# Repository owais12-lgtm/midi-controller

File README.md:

# midi-controller
A MIDI keyboard is basically just a controller. You can use it to trigger notes on a synth or plugin, you can assign the encoder to volume, LFO rate or anything else. So if you don't connect it to anything you won't get any sound.

tldr: its a smaller more weirder keyboard that can help you make music!

# features
- 6 rotary knobs for menu/Midi control
- 4 sliders
- 25 macro keys
- rp2040 based micro controller 
- choc switches
# Images

# CAD

https://www.tinkercad.com/things/4G5PN0rRYm5-midi-controller-v2

# BOM
| Name | Purpose | Quantity | Total Cost (USD) | Link | Distributor |
|------|---------|----------|-----------------|------|-------------|
| switch | switch | 30 | $10.00 | [stackskb.com](https://stackskb.com/store/ttc-low-profile-brown-switches-tactile/) | stacks |
| rpi pico | mcu | 1 | $7.00 | [robu](https://www.google.com/search?client=firefox-b-d&q=rpi+pico+robu) | robu |
| pcb | pcb | 1 | $30.00 | [lioncircuits.com](https://www.lioncircuits.com/quote) | lion pcb |

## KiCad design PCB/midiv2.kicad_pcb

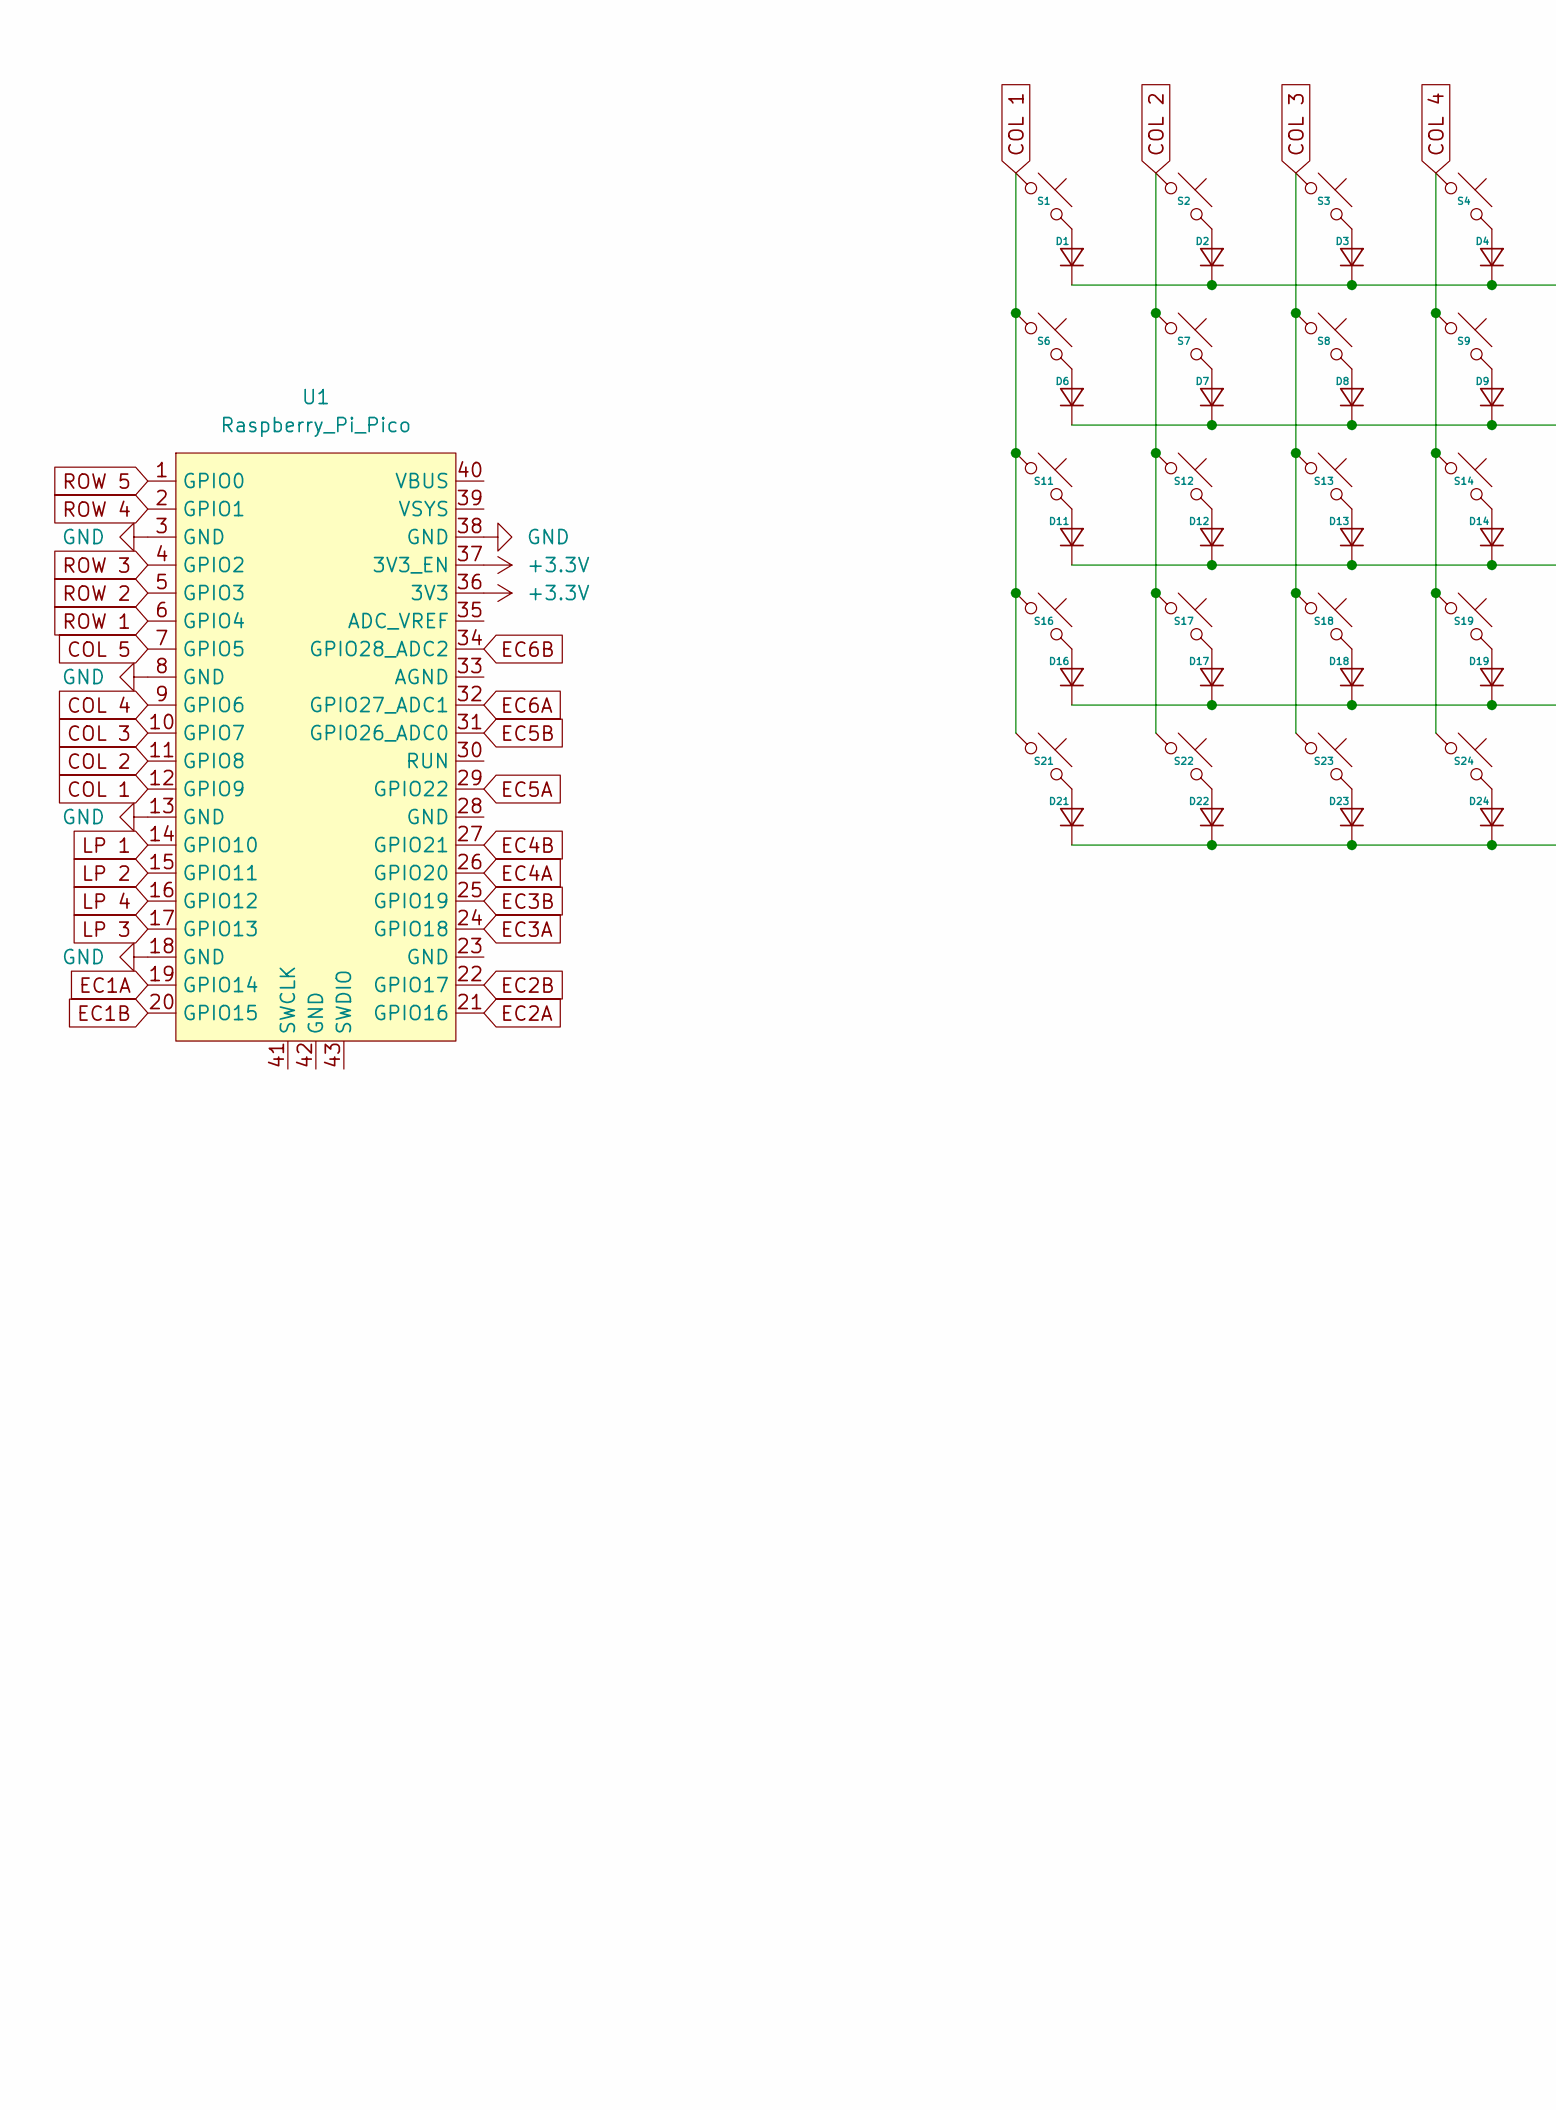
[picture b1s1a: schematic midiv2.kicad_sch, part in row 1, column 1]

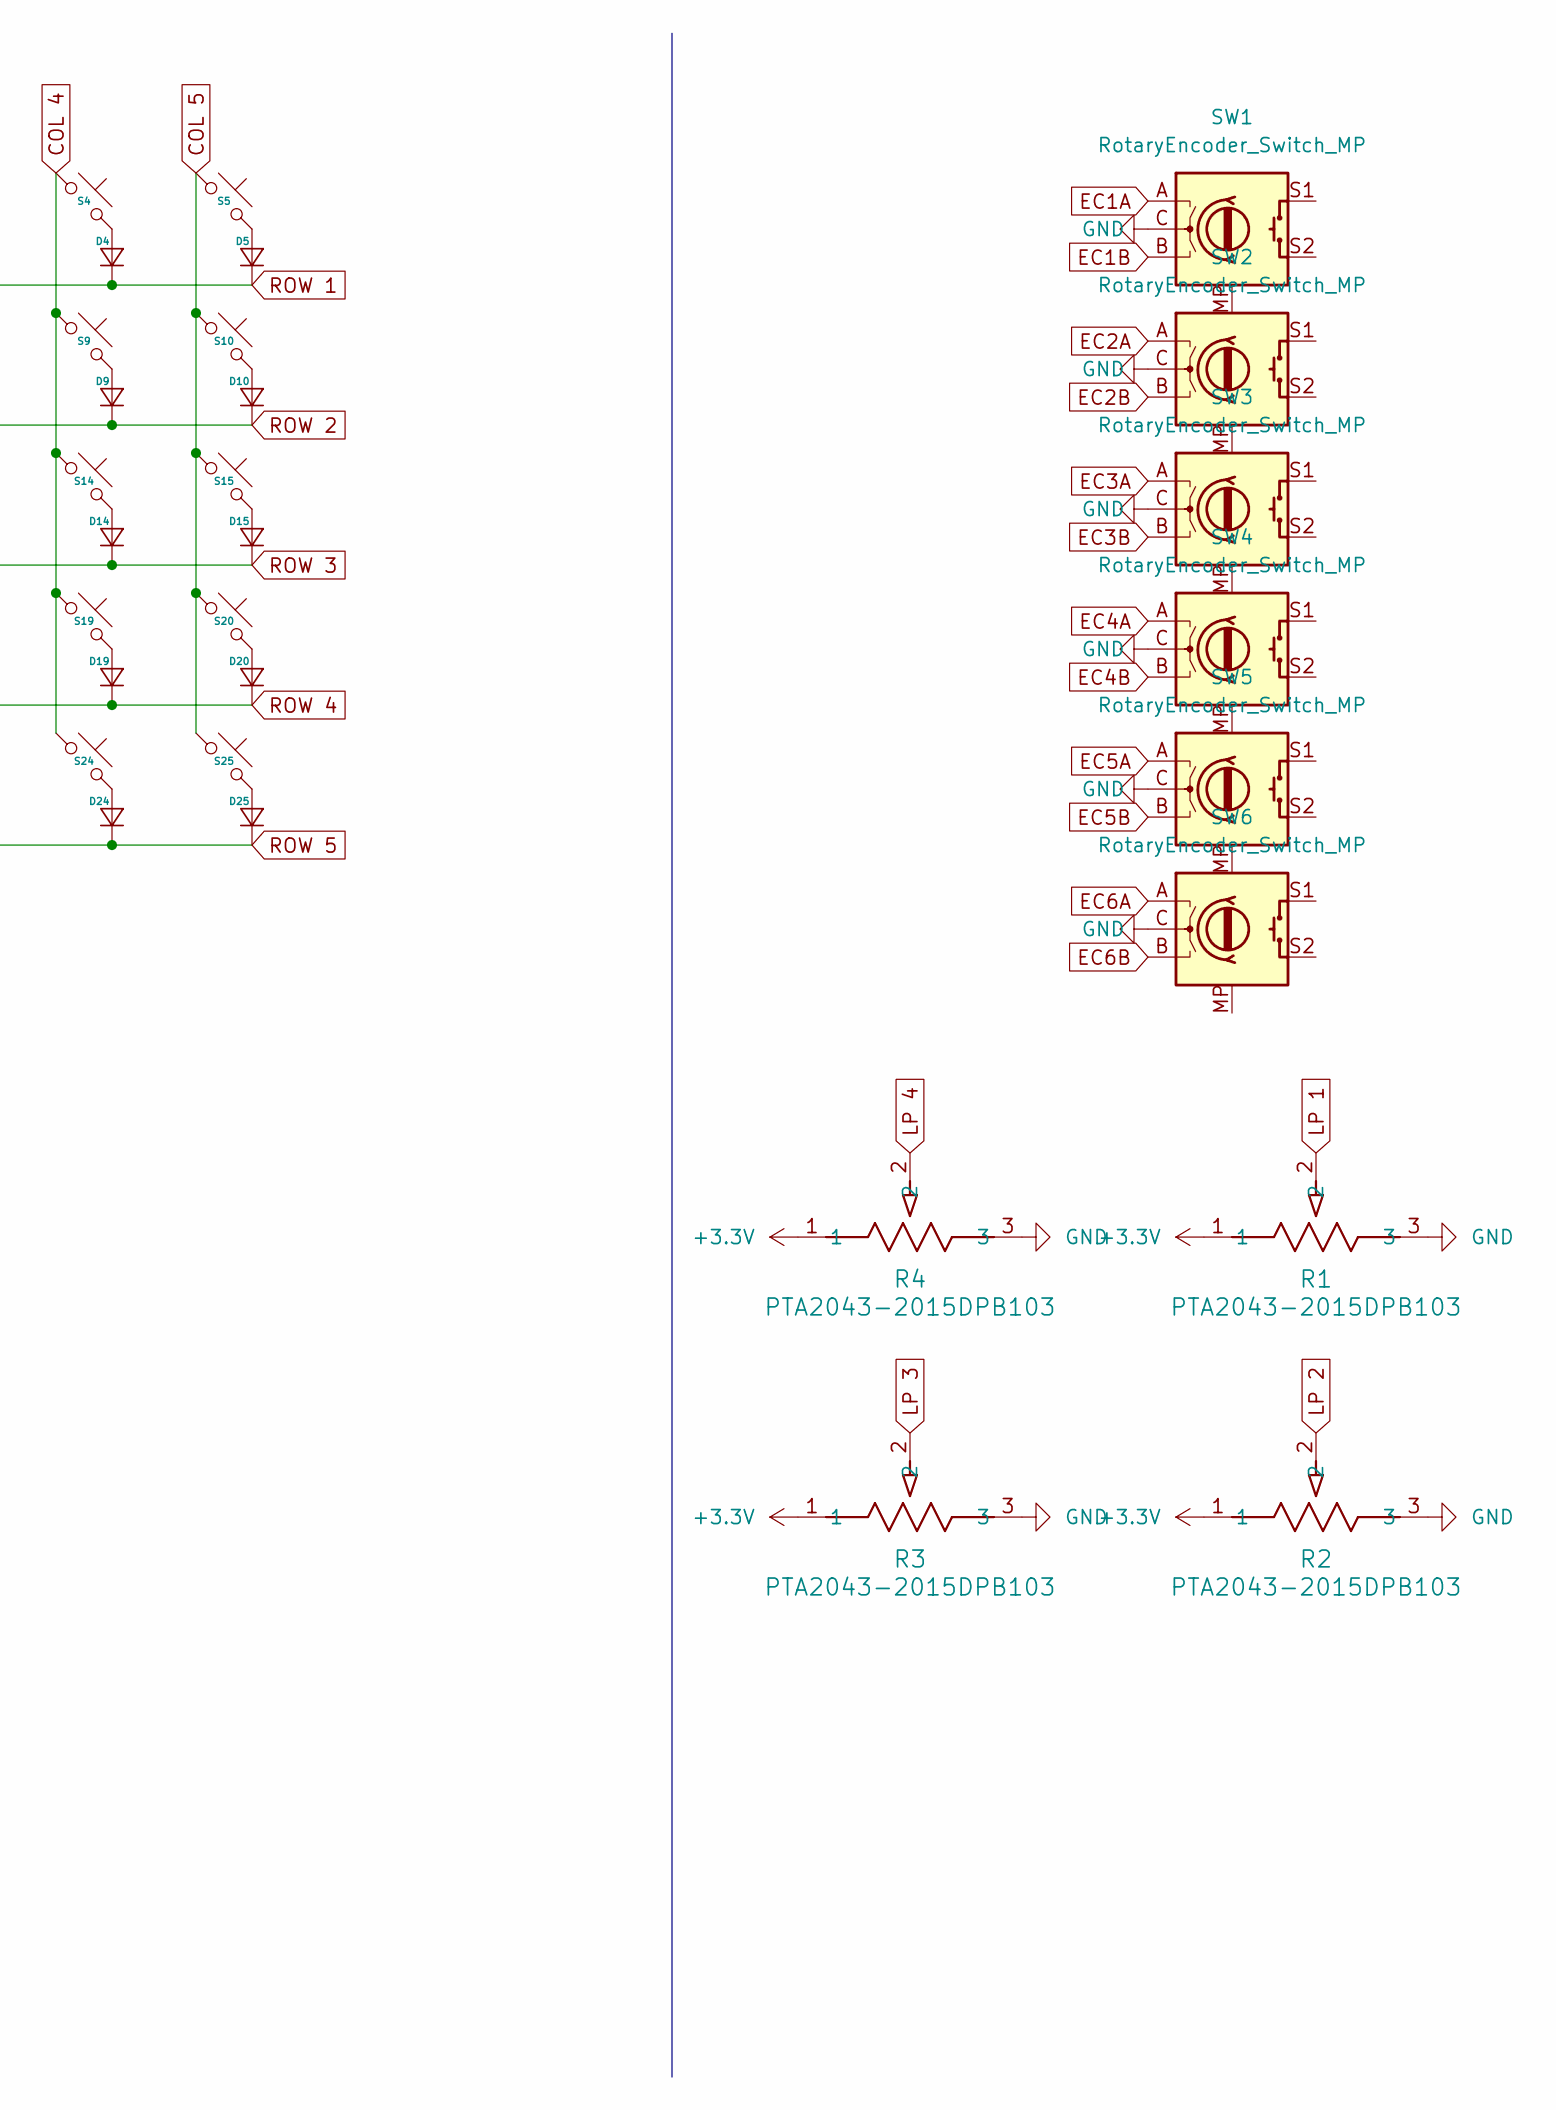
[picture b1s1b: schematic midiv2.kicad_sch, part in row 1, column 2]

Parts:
D1, D2, D3, D4, D5, D6, D7, D8, D9, D10, D11, D12, D13, D14, D15, D16, D17, D18, D19, D20, D21, D22, D23, D24, D25: Diode_DO-35
R1, R2, R3, R4: PTA2043-2015DPB103; POT_PTA2043
S1, S2, S3, S4, S5, S6, S7, S8, S9, S10, S11, S12, S13, S14, S15, S16, S17, S18, S19, S20, S21, S22, S23, S24, S25: SW_MX_LowProfile_THT
SW1, SW2, SW3, SW4, SW5, SW6: RotaryEncoder_Switch_MP; RotaryEncoder_Alps_EC11E-Switch_Vertical_H20mm_MountingHoles
U1: Raspberry_Pi_Pico

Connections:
+3.3V: R1.1, R2.1, R3.1, R4.1, U1.36 (3V3), U1.37 (3V3_EN)
COL 1: S1.1, S6.1, S11.1, S16.1, S21.1, U1.12 (GPIO9)
COL 2: S2.1, S7.1, S12.1, S17.1, S22.1, U1.11 (GPIO8)
COL 3: S3.1, S8.1, S13.1, S18.1, S23.1, U1.10 (GPIO7)
COL 4: S4.1, S9.1, S14.1, S19.1, S24.1, U1.9 (GPIO6)
COL 5: S5.1, S10.1, S15.1, S20.1, S25.1, U1.7 (GPIO5)
EC1A: SW1.A, U1.19 (GPIO14)
EC1B: SW1.B, U1.20 (GPIO15)
EC2A: SW2.A, U1.21 (GPIO16)
EC2B: SW2.B, U1.22 (GPIO17)
EC3A: SW3.A, U1.24 (GPIO18)
EC3B: SW3.B, U1.25 (GPIO19)
EC4A: SW4.A, U1.26 (GPIO20)
EC4B: SW4.B, U1.27 (GPIO21)
EC5A: SW5.A, U1.29 (GPIO22)
EC5B: SW5.B, U1.31 (GPIO26_ADC0)
EC6A: SW6.A, U1.32 (GPIO27_ADC1)
EC6B: SW6.B, U1.34 (GPIO28_ADC2)
GND: R1.3, R2.3, R3.3, R4.3, SW1.C, SW2.C, SW3.C, SW4.C, SW5.C, SW6.C, U1.3 (GND), U1.8 (GND), U1.13 (GND), U1.18 (GND), U1.38 (GND)
LP 1: R1.2, U1.14 (GPIO10)
LP 2: R2.2, U1.15 (GPIO11)
LP 3: R3.2, U1.17 (GPIO13)
LP 4: R4.2, U1.16 (GPIO12)
unnamed: D1.2 (A), S1.2
unnamed: D2.2 (A), S2.2
unnamed: D3.2 (A), S3.2
unnamed: D4.2 (A), S4.2
unnamed: D5.2 (A), S5.2
unnamed: D6.2 (A), S6.2
unnamed: D7.2 (A), S7.2
unnamed: D8.2 (A), S8.2
unnamed: D9.2 (A), S9.2
unnamed: D10.2 (A), S10.2
unnamed: D11.2 (A), S11.2
unnamed: D12.2 (A), S12.2
unnamed: D13.2 (A), S13.2
unnamed: D14.2 (A), S14.2
unnamed: D15.2 (A), S15.2
unnamed: D16.2 (A), S16.2
unnamed: D17.2 (A), S17.2
unnamed: D18.2 (A), S18.2
unnamed: D19.2 (A), S19.2
unnamed: D20.2 (A), S20.2
unnamed: D21.2 (A), S21.2
unnamed: D22.2 (A), S22.2
unnamed: D23.2 (A), S23.2
unnamed: D24.2 (A), S24.2
unnamed: D25.2 (A), S25.2
ROW 1: D1.1 (K), D2.1 (K), D3.1 (K), D4.1 (K), D5.1 (K), U1.6 (GPIO4)
ROW 2: D6.1 (K), D7.1 (K), D8.1 (K), D9.1 (K), D10.1 (K), U1.5 (GPIO3)
ROW 3: D11.1 (K), D12.1 (K), D13.1 (K), D14.1 (K), D15.1 (K), U1.4 (GPIO2)
ROW 4: D16.1 (K), D17.1 (K), D18.1 (K), D19.1 (K), D20.1 (K), U1.2 (GPIO1)
ROW 5: D21.1 (K), D22.1 (K), D23.1 (K), D24.1 (K), D25.1 (K), U1.1 (GPIO0)

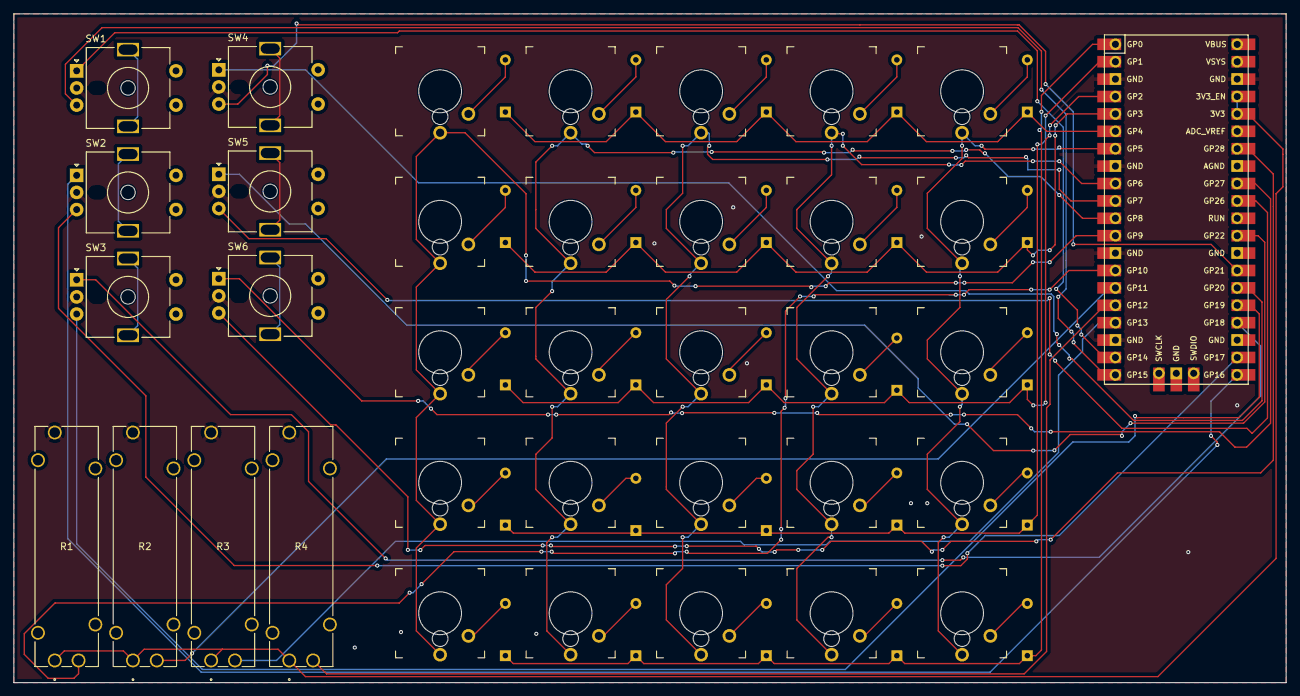
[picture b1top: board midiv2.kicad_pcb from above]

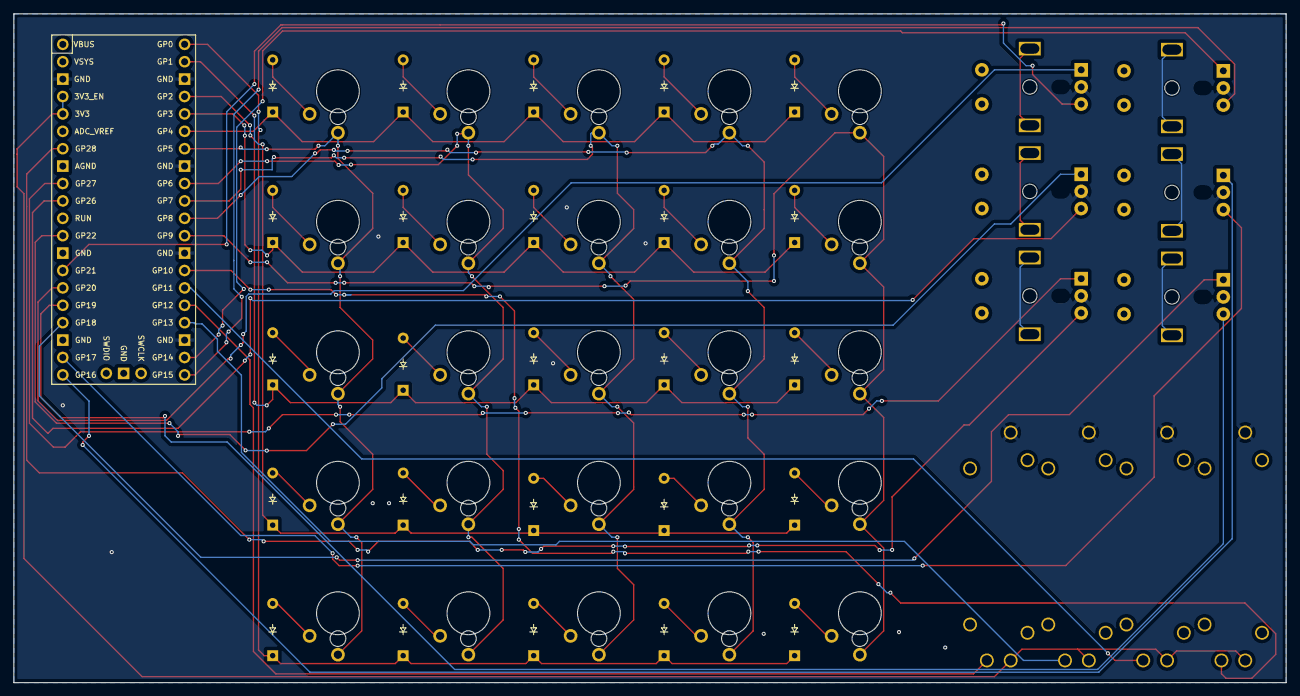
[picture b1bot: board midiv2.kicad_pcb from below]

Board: 2 copper layers, 185.7 x 97.6 mm, 61 parts (25 on the bottom side), 53 nets.
